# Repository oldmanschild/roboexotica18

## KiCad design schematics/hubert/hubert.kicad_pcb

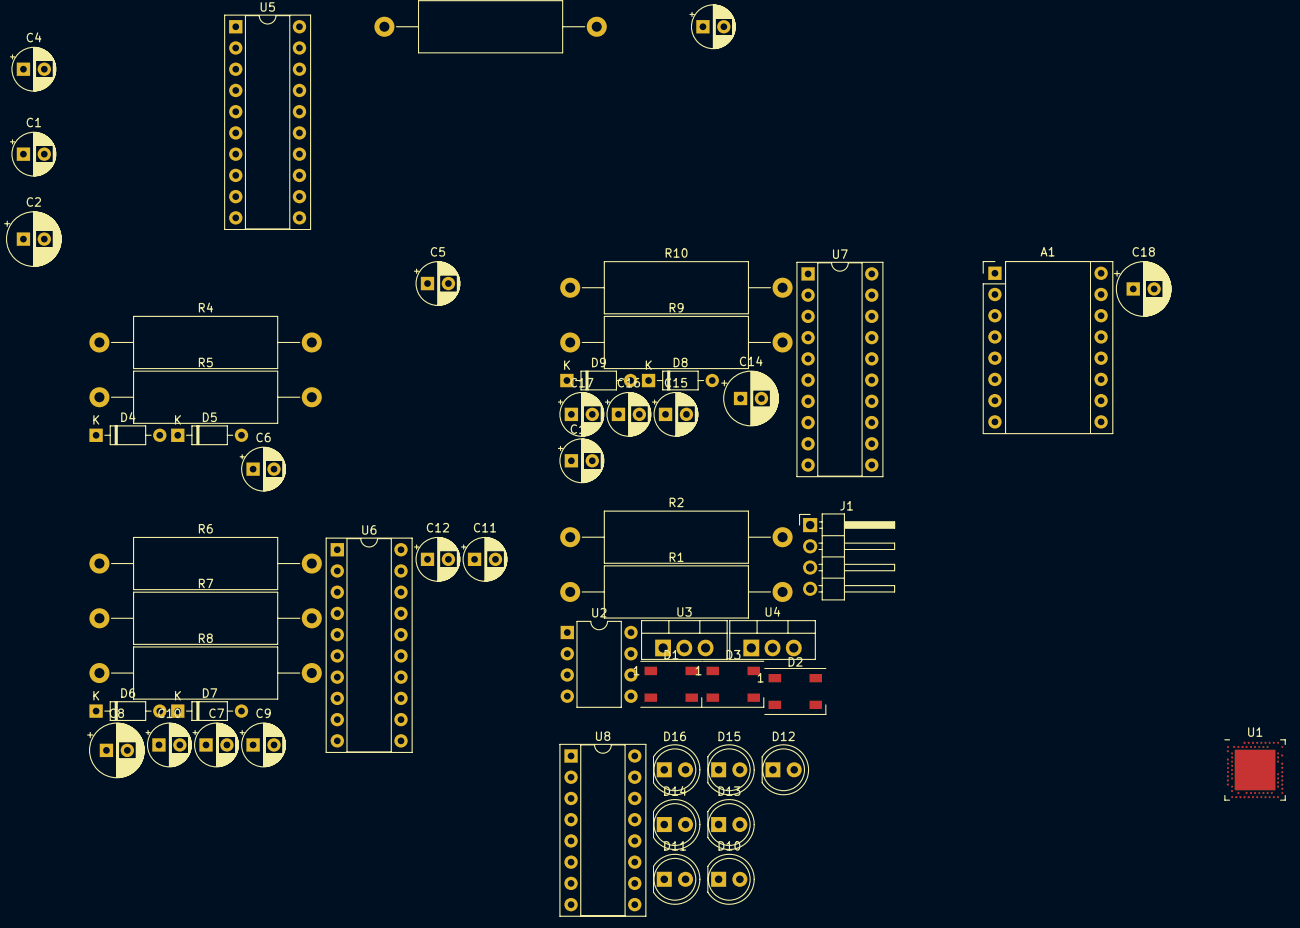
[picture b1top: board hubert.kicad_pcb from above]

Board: 2 copper layers, 54 parts (0 on the bottom side), 66 nets, no tracks yet.

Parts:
A1: Pololu_Breakout_A4988; Pololu_Breakout-16_15.2x20.3mm
C1, C7, C13: 100nF; CP_Radial_D5.0mm_P2.50mm
C2, C8, C14: 100uF; CP_Radial_D6.3mm_P2.50mm
C3, C4, C9, C10, C15: 5.6nF; CP_Radial_D5.0mm_P2.50mm
C5, C11, C16: 220nF; CP_Radial_D5.0mm_P2.50mm
C6, C12, C17: 10nF; CP_Radial_D5.0mm_P2.50mm
C18: 47uF; CP_Radial_D6.3mm_P2.50mm
D1, D2, D3: WS2812B; LED_WS2812B_PLCC4_5.0x5.0mm_P3.2mm
D4, D5, D6, D7, D8, D9: 1N4148; D_DO-35_SOD27_P7.62mm_Horizontal
D10, D11, D12, D13, D14, D15, D16: LED; LED_D5.0mm
J1: Conn_01x04_Female; PinHeader_1x04_P2.54mm_Horizontal
R1, R2: 10K; R_Axial_DIN0617_L17.0mm_D6.0mm_P25.40mm_Horizontal
R3, R4, R6, R7, R9: 100K; R_Axial_DIN0617_L17.0mm_D6.0mm_P25.40mm_Horizontal
R5, R8, R10: 100; R_Axial_DIN0617_L17.0mm_D6.0mm_P25.40mm_Horizontal
U1: nRF52840; Nordic_AQFN-73-1EP_7x7mm_P0.5mm
U2: LTV-827; DIP-8_W7.62mm
U3: LM1117-3.3; TO-220-3_Vertical
U4: LM7805_TO220; TO-220-3_Vertical
U5, U6, U7: L6205N; DIP-20_W7.62mm_Socket
U8: ULN2003A; DIP-16_W7.62mm_Socket

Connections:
+3V3: A1.2, A1.13, A1.14, D1.1, D2.1, D3.1, D10.2, D11.2, D12.2, D13.2, D14.2, D15.2, D16.2, R1.1, R2.1, U1.A22, U1.AD14, U1.AD23, U1.B1, U1.W1, U3.2
+12V: A1.8, C18.1, U3.3, U4.1
+24V: C13.1, C14.1, C16.1, D9.2, U7.14, U7.17
/12V Pump Block 1/ENA: R3.1, U5.20
/12V Pump Block 1/ENABLEA: C3.1, R3.2, U1.AD8
/12V Pump Block 1/ENABLEB: C4.1, R4.2, U1.AC9
/12V Pump Block 1/ENB: R4.1, U5.11
/12V Pump Block 1/INPUT1A: U1.AD10, U5.1
/12V Pump Block 1/INPUT1B: U1.AC11, U5.9
/12V Pump Block 1/INPUT2A: U1.AD12, U5.2
/12V Pump Block 1/INPUT2B: U1.AC15, U5.10
/12V Pump Block 2/ENA: R6.1, U6.20
/12V Pump Block 2/ENABLEA: C9.1, R6.2, U1.AD16
/12V Pump Block 2/ENABLEB: C10.1, R7.2, U1.AC17
/12V Pump Block 2/ENB: R7.1, U6.11
/12V Pump Block 2/INPUT1A: U1.AD18, U6.1
/12V Pump Block 2/INPUT1B: U1.AC19, U6.9
/12V Pump Block 2/INPUT2A: U1.AD20, U6.2
/12V Pump Block 2/INPUT2B: U1.AC21, U6.10
/24V Pump Block/ENA: R9.1, U7.20
/24V Pump Block/ENABLEA: C15.1, R9.2, U1.Y23
/24V Pump Block/INPUT1A: U1.W24, U7.1
/24V Pump Block/INPUT2A: U1.V23, U7.2
/Aspirin Dispenser/DIRECTION: A1.16, U1.R24
/Aspirin Dispenser/ENABLE: A1.9, U1.U24
/Aspirin Dispenser/MS1: A1.10, U1.P23
/Aspirin Dispenser/MS2: A1.11, U1.P2
/Aspirin Dispenser/MS3: A1.12, U1.A20
/Aspirin Dispenser/STEP: A1.15, U1.T23
/P0.06: R1.2, U1.L1, U2.8
/P0.26: U1.G1, U8.2
/P0.27: U1.H2, U8.1
/P0.31: R2.2, U1.A8, U2.6
/P1.11: U1.B19, U8.7
/P1.12: U1.B17, U8.6
/P1.13: U1.A16, U8.5
/P1.14: U1.B15, U8.4
/P1.15: U1.A14, U8.3
GND: A1.1, A1.7, C1.2, C2.2, C3.2, C4.2, C7.2, C8.2, C9.2, C10.2, C13.2, C14.2, C15.2, C18.2, D1.3, D2.3, D3.3, U1.B7, U1.EP, U2.5, U2.7, U3.1, U4.2, U5.3, U5.5, U5.6, U5.8, U5.15, U5.16, U6.3, U6.5, U6.6, U6.8, U6.15, U6.16, U7.3, U7.5, U7.6, U7.8, U7.9, U7.10, U7.11, U7.15, U7.16, U8.8, U8.9
unnamed: C5.2, D4.1, U5.12
unnamed: C6.1, R5.2
unnamed: C6.2, U5.19
unnamed: C11.2, D6.1, U6.12
unnamed: C12.1, R8.2
unnamed: C12.2, U6.19
unnamed: C16.2, D8.1, U7.12
unnamed: C17.1, R10.2
unnamed: C17.2, U7.19
unnamed: D1.2, D2.4
unnamed: D1.4, U1.N1
unnamed: D2.2, D3.4
unnamed: D4.2, D5.1, R5.1
unnamed: D6.2, D7.1, R8.1
unnamed: D8.2, D9.1, R10.1
unnamed: D10.1, U8.13
unnamed: D11.1, U8.12
unnamed: D12.1, U8.16
unnamed: D13.1, U8.11
unnamed: D14.1, U8.15
unnamed: D15.1, U8.10
unnamed: D16.1, U8.14
unnamed: J1.1, U2.4
unnamed: J1.2, U2.3
unnamed: J1.3, U2.2
unnamed: J1.4, U2.1
VPUMP12: C1.1, C2.1, C5.1, C7.1, C8.1, C11.1, D5.2, D7.2, U5.14, U5.17, U6.14, U6.17

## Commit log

2018-09-07 first tests for serial communication
2018-09-15 bootstrapped robocontrol
2018-10-31 Added schematics for Hubert
2018-10-31 Added Aspirin dispenser drawings
2018-11-01 Updated jsmntrial
2018-11-05 updated schematics
2018-11-05 fixed ERC problems and added connector for input pins
2018-11-05 started working on layout
